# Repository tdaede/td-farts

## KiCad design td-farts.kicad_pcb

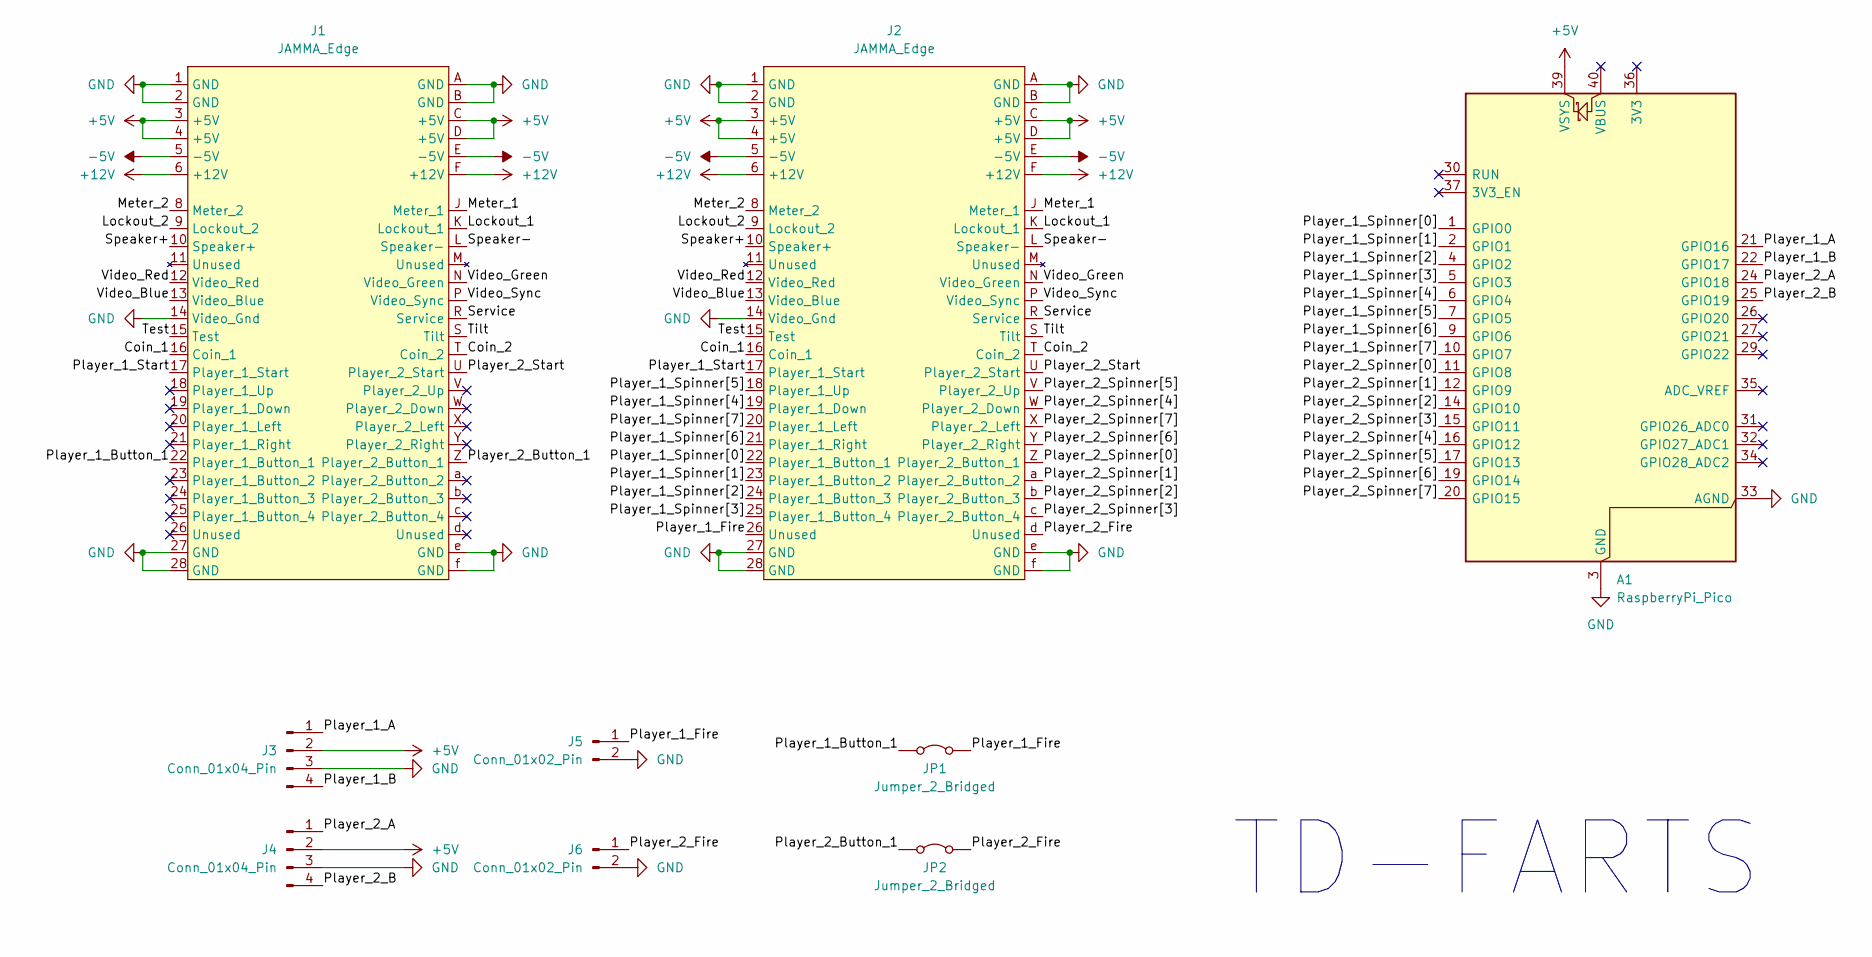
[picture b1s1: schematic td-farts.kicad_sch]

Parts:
A1: RaspberryPi_Pico; RaspberryPi_Pico_Common_Unspecified
J1: JAMMA_Edge; JAMMA
J2: JAMMA_Edge; JAMMA_Hirose_Edge
J3, J4: Conn_01x04_Pin; Molex_KK-396_5273-04A_1x04_P3.96mm_Vertical
J5, J6: Conn_01x02_Pin; Molex_KK-396_5273-02A_1x02_P3.96mm_Vertical
JP1, JP2: Jumper_2_Bridged; SolderJumper-2_P1.3mm_Bridged_Pad1.0x1.5mm

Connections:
+5V: A1.39 (VSYS), J1.3 (+5V), J1.4 (+5V), J1.C (+5V), J1.D (+5V), J2.3 (+5V), J2.4 (+5V), J2.C (+5V), J2.D (+5V), J3.2, J4.2
+12V: J1.6 (+12V), J1.F (+12V), J2.6 (+12V), J2.F (+12V)
-5V: J1.5 (-5V), J1.E (-5V), J2.5 (-5V), J2.E (-5V)
/Coin_1: J1.16 (Coin_1), J2.16 (Coin_1)
/Coin_2: J1.T (Coin_2), J2.T (Coin_2)
/Lockout_1: J1.K (Lockout_1), J2.K (Lockout_1)
/Lockout_2: J1.9 (Lockout_2), J2.9 (Lockout_2)
/Meter_1: J1.J (Meter_1), J2.J (Meter_1)
/Meter_2: J1.8 (Meter_2), J2.8 (Meter_2)
/Player_1_A: A1.21 (GPIO16), J3.1
/Player_1_B: A1.22 (GPIO17), J3.4
/Player_1_Button_1: J1.22 (Player_1_Button_1), JP1.1 (A)
/Player_1_Fire: J2.26 (Unused), J5.1, JP1.2 (B)
/Player_1_Spinner[0]: A1.1 (GPIO0), J2.22 (Player_1_Button_1)
/Player_1_Spinner[1]: A1.2 (GPIO1), J2.23 (Player_1_Button_2)
/Player_1_Spinner[2]: A1.4 (GPIO2), J2.24 (Player_1_Button_3)
/Player_1_Spinner[3]: A1.5 (GPIO3), J2.25 (Player_1_Button_4)
/Player_1_Spinner[4]: A1.6 (GPIO4), J2.19 (Player_1_Down)
/Player_1_Spinner[5]: A1.7 (GPIO5), J2.18 (Player_1_Up)
/Player_1_Spinner[6]: A1.9 (GPIO6), J2.21 (Player_1_Right)
/Player_1_Spinner[7]: A1.10 (GPIO7), J2.20 (Player_1_Left)
/Player_1_Start: J1.17 (Player_1_Start), J2.17 (Player_1_Start)
/Player_2_A: A1.24 (GPIO18), J4.1
/Player_2_B: A1.25 (GPIO19), J4.4
/Player_2_Button_1: J1.Z (Player_2_Button_1), JP2.1 (A)
/Player_2_Fire: J2.d (Unused), J6.1, JP2.2 (B)
/Player_2_Spinner[0]: A1.11 (GPIO8), J2.Z (Player_2_Button_1)
/Player_2_Spinner[1]: A1.12 (GPIO9), J2.a (Player_2_Button_2)
/Player_2_Spinner[2]: A1.14 (GPIO10), J2.b (Player_2_Button_3)
/Player_2_Spinner[3]: A1.15 (GPIO11), J2.c (Player_2_Button_4)
/Player_2_Spinner[4]: A1.16 (GPIO12), J2.W (Player_2_Down)
/Player_2_Spinner[5]: A1.17 (GPIO13), J2.V (Player_2_Up)
/Player_2_Spinner[6]: A1.19 (GPIO14), J2.Y (Player_2_Right)
/Player_2_Spinner[7]: A1.20 (GPIO15), J2.X (Player_2_Left)
/Player_2_Start: J1.U (Player_2_Start), J2.U (Player_2_Start)
/Service: J1.R (Service), J2.R (Service)
/Speaker+: J1.10 (Speaker+), J2.10 (Speaker+)
/Speaker-: J1.L (Speaker-), J2.L (Speaker-)
/Test: J1.15 (Test), J2.15 (Test)
/Tilt: J1.S (Tilt), J2.S (Tilt)
/Video_Blue: J1.13 (Video_Blue), J2.13 (Video_Blue)
/Video_Green: J1.N (Video_Green), J2.N (Video_Green)
/Video_Red: J1.12 (Video_Red), J2.12 (Video_Red)
/Video_Sync: J1.P (Video_Sync), J2.P (Video_Sync)
GND: A1.3 (GND), A1.8 (GND), A1.13 (GND), A1.18 (GND), A1.23 (GND), A1.28 (GND), A1.33 (AGND), A1.38 (GND), J1.1 (GND), J1.2 (GND), J1.14 (Video_Gnd), J1.27 (GND), J1.28 (GND), J1.A (GND), J1.B (GND), J1.e (GND), J1.f (GND), J2.1 (GND), J2.2 (GND), J2.14 (Video_Gnd), J2.27 (GND), J2.28 (GND), J2.A (GND), J2.B (GND), J2.e (GND), J2.f (GND), J3.3, J4.3, J5.2, J6.2

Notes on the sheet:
TD-FARTS

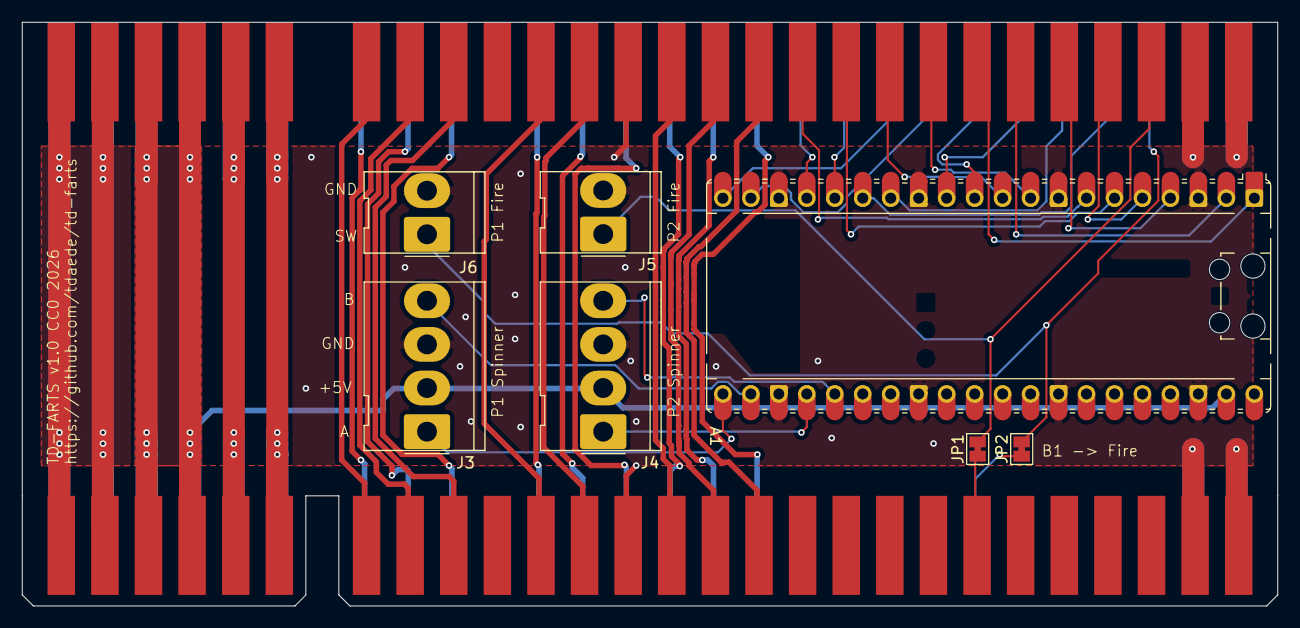
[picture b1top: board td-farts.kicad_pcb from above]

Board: 2 copper layers, 114.0 x 53.0 mm, 9 parts (0 on the bottom side), 45 nets.

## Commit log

2026-06-28 Add firmware
2026-06-28 switch to driving gpio all at once and push pull
2026-06-28 Divide spinner speed by 2
2026-06-28 Read all inputs at once
2026-06-28 Remove stdio support

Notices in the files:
td-farts.kicad_pcb:
TD-FARTS v1.0 CC0 2026
